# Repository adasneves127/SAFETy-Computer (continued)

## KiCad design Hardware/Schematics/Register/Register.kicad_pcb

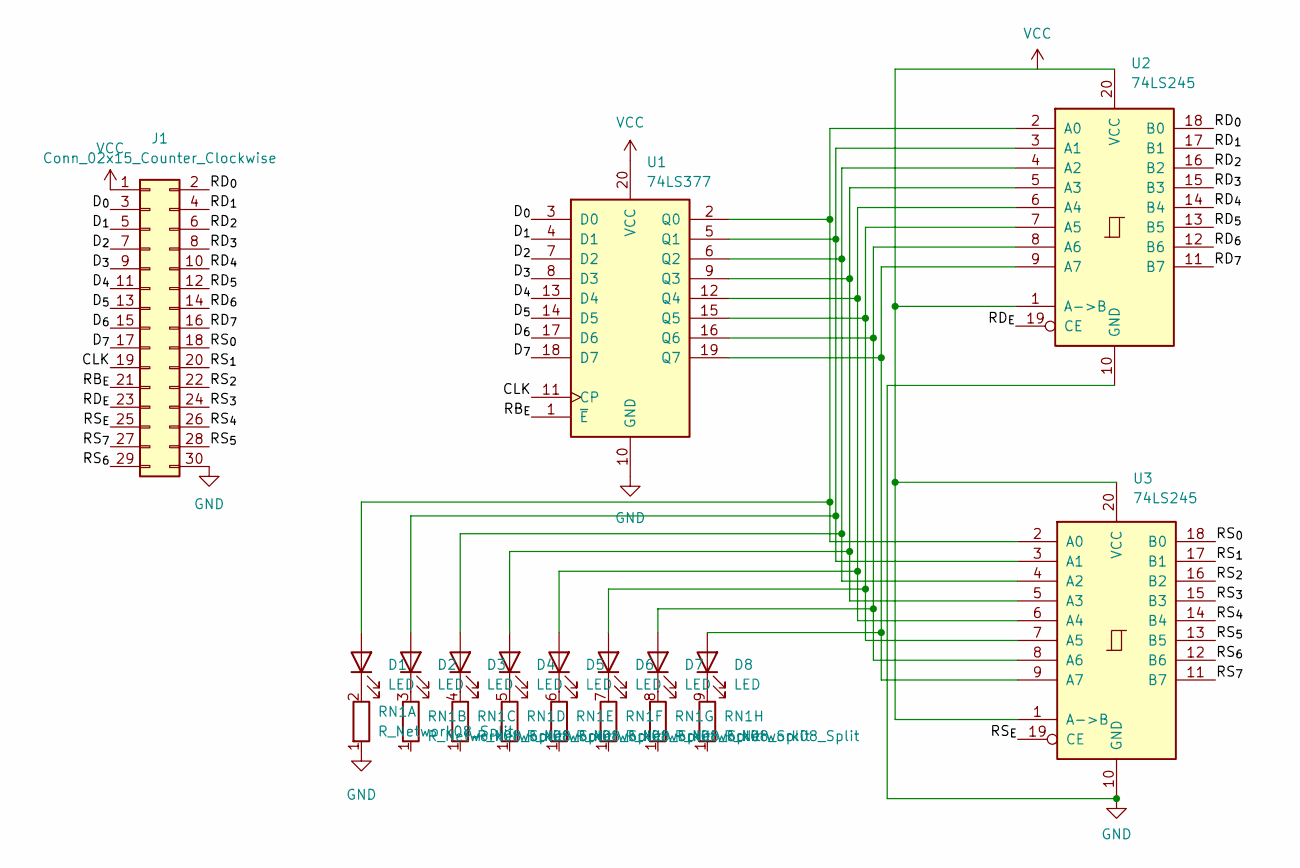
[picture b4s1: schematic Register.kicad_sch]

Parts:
D1, D2, D3, D4, D5, D6, D7, D8: LED; LED_D5.0mm
J1: Conn_02x15_Counter_Clockwise; PinHeader_2x15_P2.54mm_Vertical
RN1: R_Network08_Split; R_Array_SIP9
U1: 74LS377; DIP-20_W7.62mm_Socket_LongPads
U2, U3: 74LS245; DIP-20_W7.62mm_Socket_LongPads

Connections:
/CLK: J1.19, U1.11 (CP)
/D_{0}: J1.3, U1.3 (D0)
/D_{1}: J1.5, U1.4 (D1)
/D_{2}: J1.7, U1.7 (D2)
/D_{3}: J1.9, U1.8 (D3)
/D_{4}: J1.11, U1.13 (D4)
/D_{5}: J1.13, U1.14 (D5)
/D_{6}: J1.15, U1.17 (D6)
/D_{7}: J1.17, U1.18 (D7)
/RB_{E}: J1.21, U1.1 (~E)
/RD_{0}: J1.2, U2.18 (B0)
/RD_{1}: J1.4, U2.17 (B1)
/RD_{2}: J1.6, U2.16 (B2)
/RD_{3}: J1.8, U2.15 (B3)
/RD_{4}: J1.10, U2.14 (B4)
/RD_{5}: J1.12, U2.13 (B5)
/RD_{6}: J1.14, U2.12 (B6)
/RD_{7}: J1.16, U2.11 (B7)
/RD_{E}: J1.23, U2.19 (CE)
/RS_{0}: J1.18, U3.18 (B0)
/RS_{1}: J1.20, U3.17 (B1)
/RS_{2}: J1.22, U3.16 (B2)
/RS_{3}: J1.24, U3.15 (B3)
/RS_{4}: J1.26, U3.14 (B4)
/RS_{5}: J1.28, U3.13 (B5)
/RS_{6}: J1.29, U3.12 (B6)
/RS_{7}: J1.27, U3.11 (B7)
/RS_{E}: J1.25, U3.19 (CE)
GND: J1.30, RN1.1 (R1.1), U1.10 (GND), U2.10 (GND), U3.10 (GND)
unnamed: D1.1 (K), RN1.2 (R1.2)
unnamed: D2.1 (K), RN1.3 (R2.2)
unnamed: D3.1 (K), RN1.4 (R3.2)
unnamed: D4.1 (K), RN1.5 (R4.2)
unnamed: D5.1 (K), RN1.6 (R5.2)
unnamed: D6.1 (K), RN1.7 (R6.2)
unnamed: D7.1 (K), RN1.8 (R7.2)
unnamed: D8.1 (K), RN1.9 (R8.2)
unnamed: D1.2 (A), U1.2 (Q0), U2.2 (A0), U3.2 (A0)
unnamed: D2.2 (A), U1.5 (Q1), U2.3 (A1), U3.3 (A1)
unnamed: D3.2 (A), U1.6 (Q2), U2.4 (A2), U3.4 (A2)
unnamed: D4.2 (A), U1.9 (Q3), U2.5 (A3), U3.5 (A3)
unnamed: D5.2 (A), U1.12 (Q4), U2.6 (A4), U3.6 (A4)
unnamed: D6.2 (A), U1.15 (Q5), U2.7 (A5), U3.7 (A5)
unnamed: D7.2 (A), U1.16 (Q6), U2.8 (A6), U3.8 (A6)
unnamed: D8.2 (A), U1.19 (Q7), U2.9 (A7), U3.9 (A7)

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
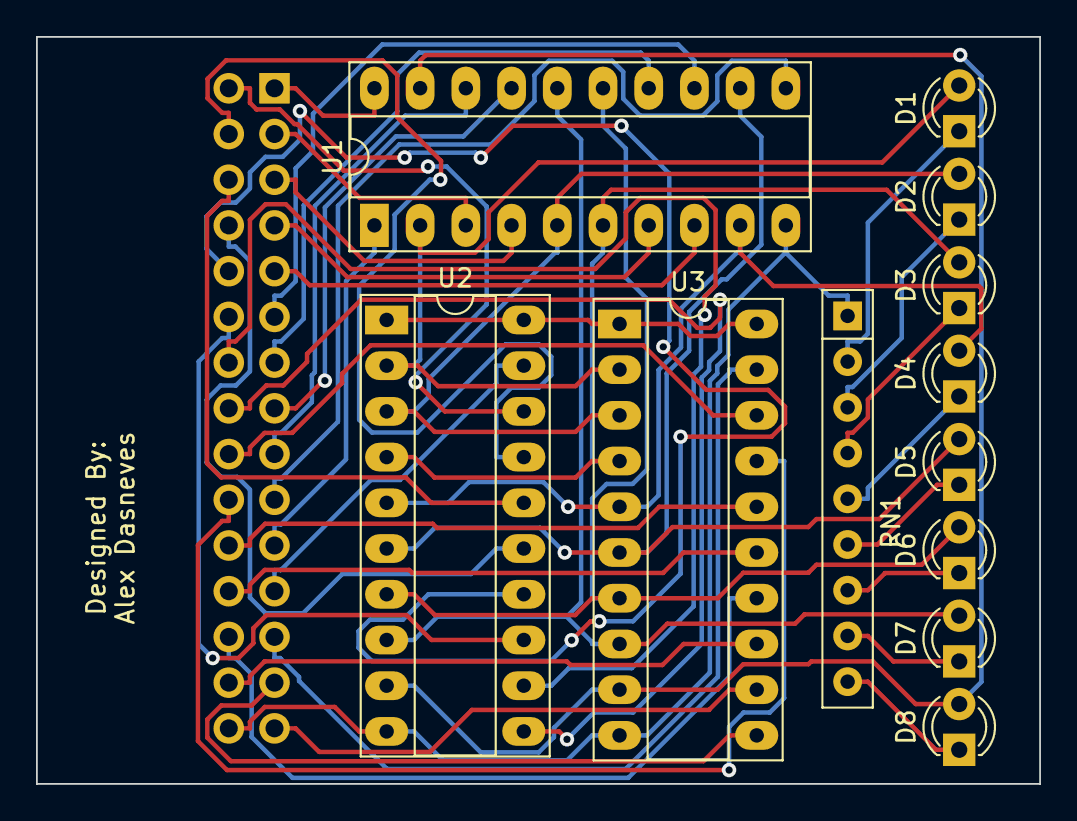
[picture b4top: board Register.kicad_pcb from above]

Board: 2 copper layers, 55.7 x 41.5 mm, 13 parts (1 on the bottom side), 47 nets.

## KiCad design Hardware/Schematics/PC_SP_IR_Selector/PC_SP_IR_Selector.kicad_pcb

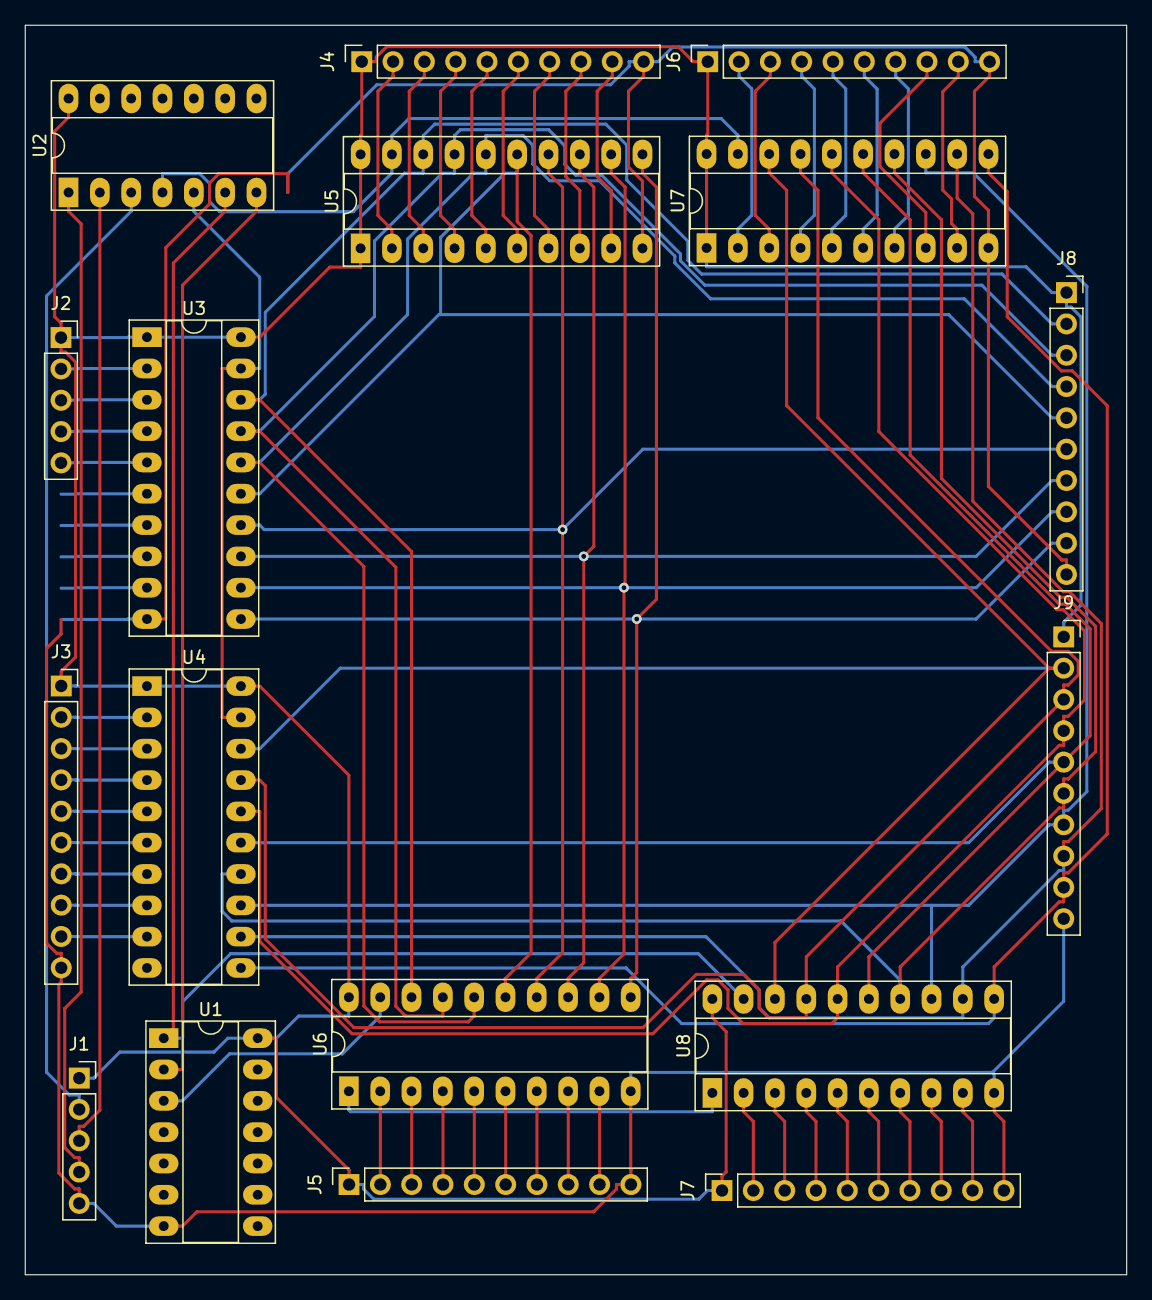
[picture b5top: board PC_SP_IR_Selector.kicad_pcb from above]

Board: 2 copper layers, 89.3 x 101.3 mm, 17 parts (0 on the bottom side), 71 nets.

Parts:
J1: Conn_01x05; PinSocket_1x05_P2.54mm_Vertical
J2: Conn_01x10; PinSocket_1x05_P2.54mm_Vertical
J3, J4, J5, J6, J7, J8, J9: Conn_01x10; PinSocket_1x10_P2.54mm_Vertical
U1: 74LS08; DIP-14_W7.62mm_Socket_LongPads
U2: 74LS139; DIP-14_W7.62mm_Socket_LongPads
U3, U4, U5, U6, U7, U8: 74LS245; DIP-20_W7.62mm_Socket_LongPads

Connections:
GND: J1.5, J3.10, J4.10, J5.10, J6.10, J7.10, J8.10, J9.10, U1.7 (GND), U2.8 (GND), U3.10 (GND), U5.10 (GND), U6.10 (GND), U7.10 (GND), U8.10 (GND)
unnamed: J1.2, U2.3 (A1)
unnamed: J1.3, U2.2 (A0)
unnamed: J1.4, U2.1 (E)
unnamed: J2.2, U3.2 (A0)
unnamed: J2.3, U3.3 (A1)
unnamed: J2.4, U3.4 (A2)
unnamed: J2.5, U3.5 (A3)
unnamed: J3.2, U4.2 (A0)
unnamed: J3.3, U4.3 (A1)
unnamed: J3.4, U4.4 (A2)
unnamed: J3.5, U4.5 (A3)
unnamed: J3.6, U4.6 (A4)
unnamed: J3.7, U4.7 (A5)
unnamed: J3.8, U4.8 (A6)
unnamed: J3.9, U4.9 (A7)
unnamed: J4.2, U5.2 (A0)
unnamed: J4.3, U5.3 (A1)
unnamed: J4.4, U5.4 (A2)
unnamed: J4.5, U5.5 (A3)
unnamed: J4.6, U5.6 (A4)
unnamed: J4.7, U5.7 (A5)
unnamed: J4.8, U5.8 (A6)
unnamed: J4.9, U5.9 (A7)
unnamed: J5.2, U6.2 (A0)
unnamed: J5.3, U6.3 (A1)
unnamed: J5.4, U6.4 (A2)
unnamed: J5.5, U6.5 (A3)
unnamed: J5.6, U6.6 (A4)
unnamed: J5.7, U6.7 (A5)
unnamed: J5.8, U6.8 (A6)
unnamed: J5.9, U6.9 (A7)
unnamed: J6.2, U7.2 (A0)
unnamed: J6.3, U7.3 (A1)
unnamed: J6.4, U7.4 (A2)
unnamed: J6.5, U7.5 (A3)
unnamed: J6.6, U7.6 (A4)
unnamed: J6.7, U7.7 (A5)
unnamed: J6.8, U7.8 (A6)
unnamed: J6.9, U7.9 (A7)
unnamed: J7.2, U8.2 (A0)
unnamed: J7.3, U8.3 (A1)
unnamed: J7.4, U8.4 (A2)
unnamed: J7.5, U8.5 (A3)
unnamed: J7.6, U8.6 (A4)
unnamed: J7.7, U8.7 (A5)
unnamed: J7.8, U8.8 (A6)
unnamed: J7.9, U8.9 (A7)
unnamed: J8.2, U3.18 (B0), U5.18 (B0), U6.18 (B0)
unnamed: J8.3, U3.17 (B1), U5.17 (B1), U6.17 (B1)
unnamed: J8.4, U3.16 (B2), U5.16 (B2), U6.16 (B2)
unnamed: J8.5, U3.15 (B3), U5.15 (B3), U6.15 (B3)
unnamed: J8.6, U3.14 (B4), U5.14 (B4), U6.14 (B4)
unnamed: J8.7, U3.13 (B5), U5.13 (B5), U6.13 (B5)
unnamed: J8.8, U3.12 (B6), U5.12 (B6), U6.12 (B6)
unnamed: J8.9, U3.11 (B7), U5.11 (B7), U6.11 (B7)
unnamed: J9.2, U4.18 (B0), U7.18 (B0), U8.18 (B0)
unnamed: J9.3, U4.17 (B1), U7.17 (B1), U8.17 (B1)
unnamed: J9.4, U4.16 (B2), U7.16 (B2), U8.16 (B2)
unnamed: J9.5, U4.15 (B3), U7.15 (B3), U8.15 (B3)
unnamed: J9.6, U4.14 (B4), U7.14 (B4), U8.14 (B4)
unnamed: J9.7, U4.13 (B5), U7.13 (B5), U8.13 (B5)
unnamed: J9.8, U4.12 (B6), U7.12 (B6), U8.12 (B6)
unnamed: J9.9, U4.11 (B7), U7.11 (B7), U8.11 (B7)
unnamed: U1.1, U2.6 (O2), U8.19 (CE)
unnamed: U1.2, U2.7 (O3)
unnamed: U1.3, U6.19 (CE)
unnamed: U2.4 (O0), U5.19 (CE), U7.19 (CE)
unnamed: U2.5 (O1), U3.19 (CE), U4.19 (CE)
unnamed: U6.1 (A->B), U8.1 (A->B)
VCC: J1.1, J2.1, J3.1, J4.1, J5.1, J6.1, J7.1, J8.1, J9.1, U1.14 (VCC), U3.1 (A->B), U3.20 (VCC), U4.1 (A->B), U4.20 (VCC), U5.1 (A->B), U5.20 (VCC), U6.20 (VCC), U7.1 (A->B), U7.20 (VCC), U8.20 (VCC)

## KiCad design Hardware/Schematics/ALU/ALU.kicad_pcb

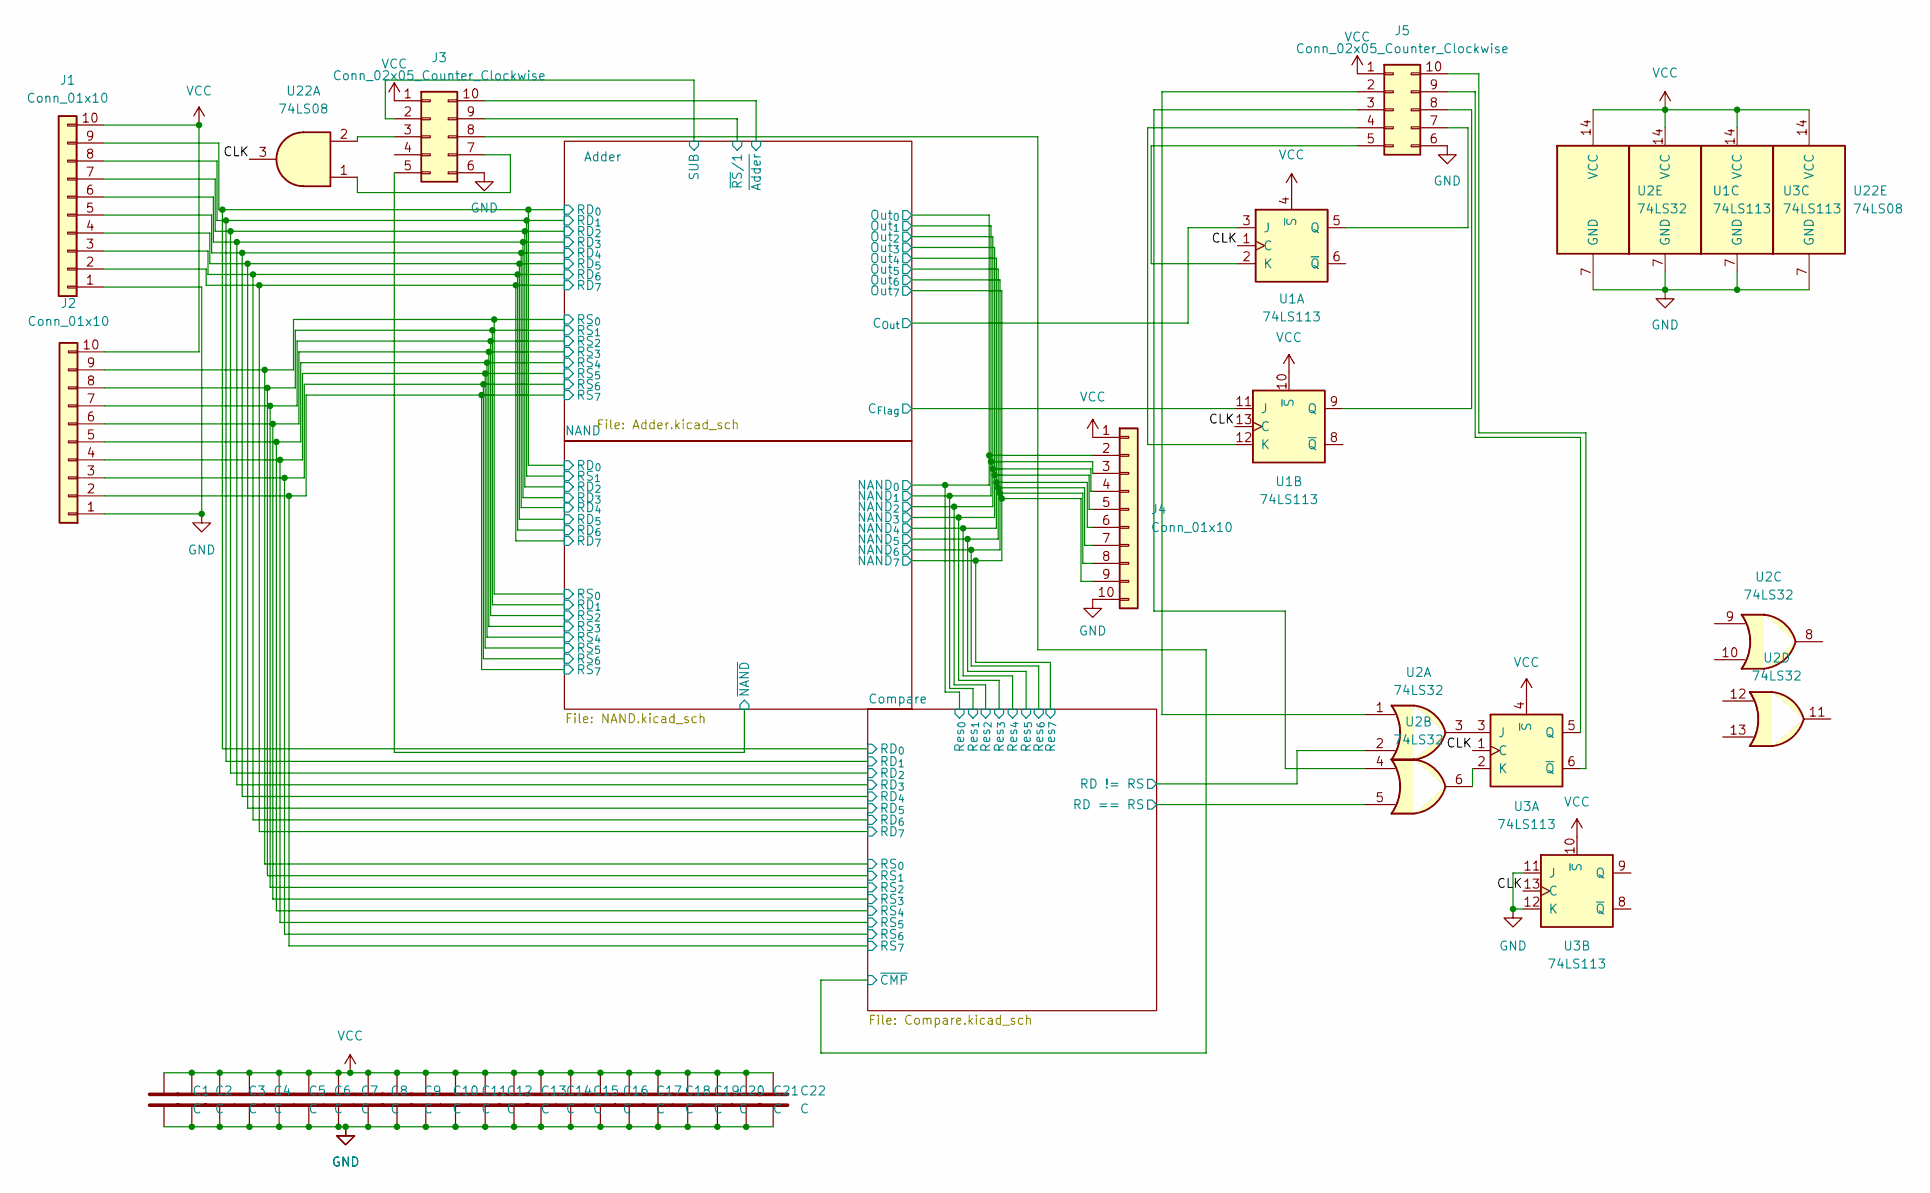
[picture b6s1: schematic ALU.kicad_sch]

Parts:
C1, C2, C3, C4, C5, C6, C7, C8, C9, C10, C11, C12, C13, C14, C15, C16, C17, C18, C19, C20, C21, C22: C; C_Rect_L9.0mm_W2.5mm_P7.50mm_MKT
J1, J2, J4: Conn_01x10; PinHeader_1x10_P2.54mm_Horizontal
J3, J5: Conn_02x05_Counter_Clockwise; PinHeader_2x05_P2.54mm_Horizontal
U1, U3: 74LS113; DIP-14_W7.62mm_Socket_LongPads
U2: 74LS32; DIP-14_W7.62mm_Socket_LongPads
U22: 74LS08; DIP-14_W7.62mm_Socket_LongPads

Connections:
/Adder/C_{Flag}: U1.11 (J); also elsewhere on the board
/Adder/C_{Out}: U1.3 (J); also elsewhere on the board
/Adder/Out_{0}: J4.2; also elsewhere on the board
/Adder/Out_{1}: J4.3; also elsewhere on the board
/Adder/Out_{2}: J4.4; also elsewhere on the board
/Adder/Out_{3}: J4.5; also elsewhere on the board
/Adder/Out_{4}: J4.6; also elsewhere on the board
/Adder/Out_{5}: J4.7; also elsewhere on the board
/Adder/Out_{6}: J4.8; also elsewhere on the board
/Adder/Out_{7}: J4.9; also elsewhere on the board
/Adder/RD_{0}: J1.9; also elsewhere on the board
/Adder/RD_{1}: J1.8; also elsewhere on the board
/Adder/RD_{2}: J1.7; also elsewhere on the board
/Adder/RD_{3}: J1.6; also elsewhere on the board
/Adder/RD_{4}: J1.5; also elsewhere on the board
/Adder/RD_{5}: J1.4; also elsewhere on the board
/Adder/RD_{6}: J1.3; also elsewhere on the board
/Adder/RD_{7}: J1.2; also elsewhere on the board
/Adder/RS_{0}: J2.9; also elsewhere on the board
/Adder/RS_{1}: J2.8; also elsewhere on the board
/Adder/RS_{2}: J2.7; also elsewhere on the board
/Adder/RS_{3}: J2.6; also elsewhere on the board
/Adder/RS_{4}: J2.5; also elsewhere on the board
/Adder/RS_{5}: J2.4; also elsewhere on the board
/Adder/RS_{6}: J2.3; also elsewhere on the board
/Adder/RS_{7}: J2.2; also elsewhere on the board
/Adder/SUB: J3.2; also elsewhere on the board
/Adder/~Adder: J3.10; also elsewhere on the board
/Adder/~RS/1: J3.9; also elsewhere on the board
/CLK: U1.1 (C), U1.13 (C), U3.1 (C), U3.13 (C), U22.3
/Compare/RD != RS: U2.2; also elsewhere on the board
/Compare/RD == RS: U2.5; also elsewhere on the board
/Compare/~CMP: J3.8; also elsewhere on the board
/NAND/~NAND: J3.5; also elsewhere on the board
GND: C1.2, C2.2, C3.2, C4.2, C5.2, C6.2, C7.2, C8.2, C9.2, C10.2, C11.2, C12.2, C13.2, C14.2, C15.2, C16.2, C17.2, C18.2, C19.2, C20.2, C21.2, C22.2, J1.1, J2.1, J3.6, J4.10, J5.6, U1.7 (GND), U2.7 (GND), U3.7 (GND), U3.11 (J), U3.12 (K), U22.7 (GND); also elsewhere on the board
unnamed: J3.3, U22.2
unnamed: J3.7, U22.1
unnamed: J5.2, U2.1
unnamed: J5.3, U2.4
unnamed: J5.4, U1.12 (K)
unnamed: J5.5, U1.2 (K)
unnamed: J5.7, U1.5 (Q)
unnamed: J5.8, U1.9 (Q)
unnamed: J5.9, U3.5 (Q)
unnamed: J5.10, U3.6 (~Q)
unnamed: U2.3, U3.3 (J)
unnamed: U2.6, U3.2 (K)
VCC: C1.1, C2.1, C3.1, C4.1, C5.1, C6.1, C7.1, C8.1, C9.1, C10.1, C11.1, C12.1, C13.1, C14.1, C15.1, C16.1, C17.1, C18.1, C19.1, C20.1, C21.1, C22.1, J1.10, J2.10, J3.1, J4.1, J5.1, U1.4 (~S), U1.10 (~S), U1.14 (VCC), U2.14 (VCC), U3.4 (~S), U3.10 (~S), U3.14 (VCC), U22.14 (VCC); also elsewhere on the board

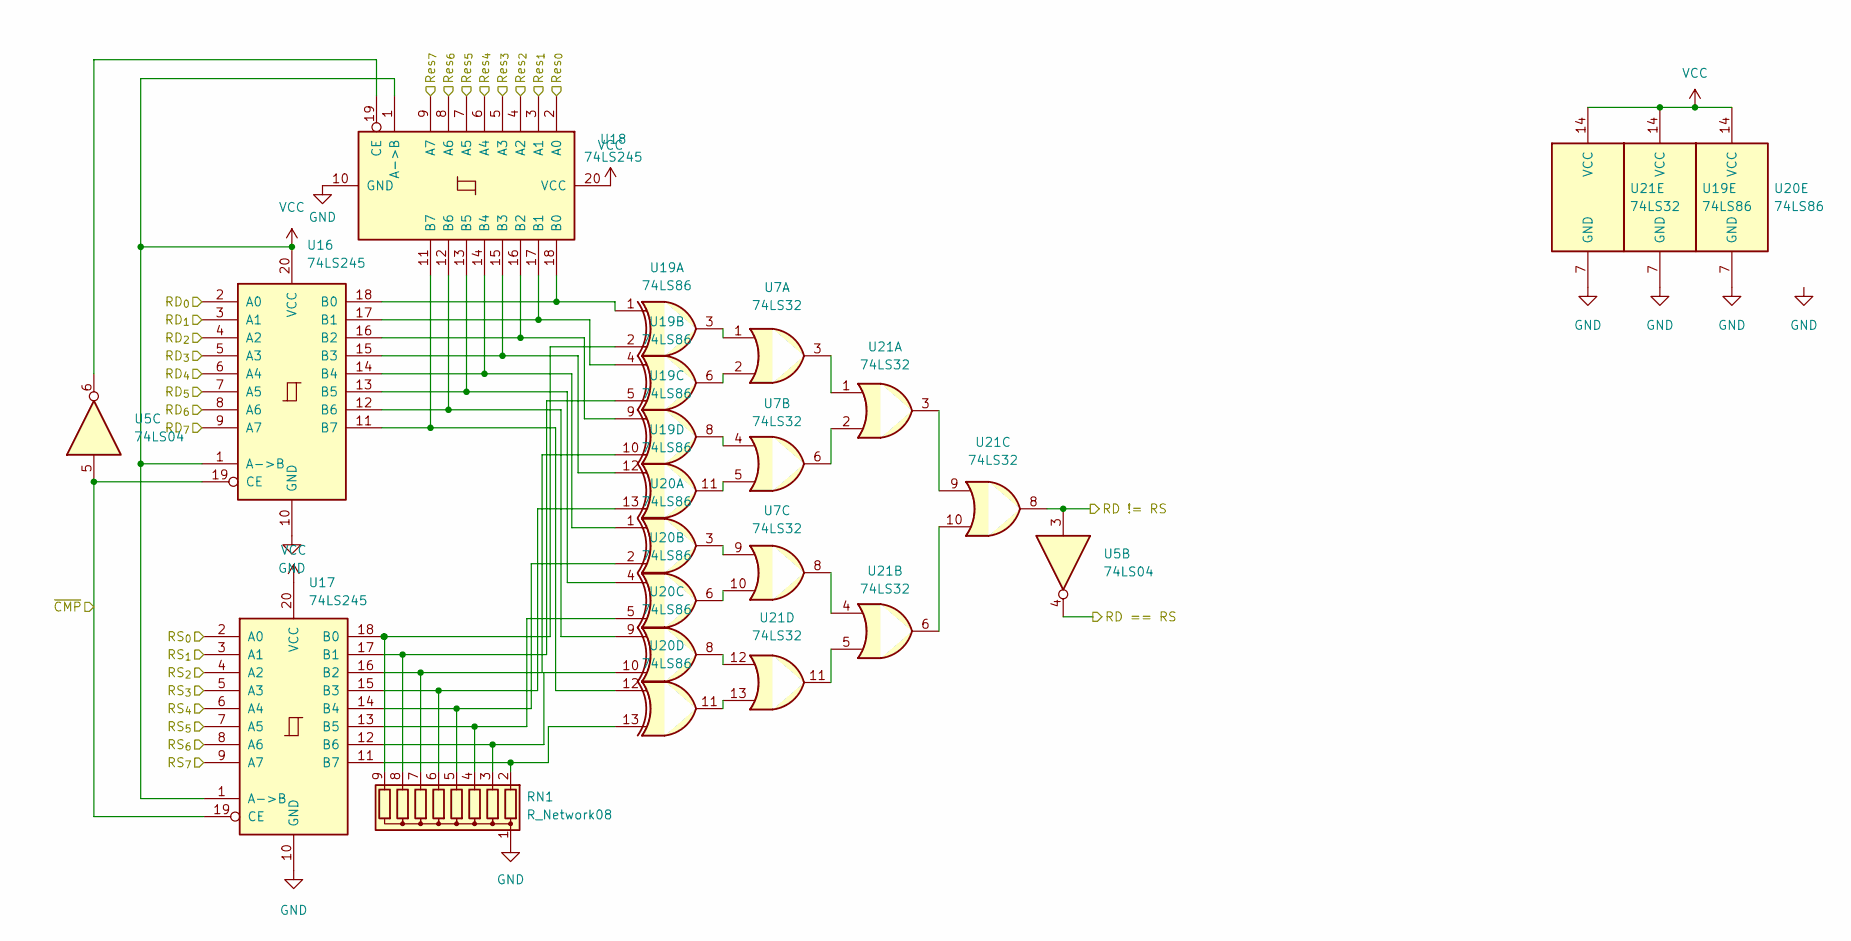
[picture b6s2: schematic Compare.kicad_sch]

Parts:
RN1: R_Network08; R_Array_SIP9
U5: 74LS04; DIP-14_W7.62mm_Socket_LongPads
U7, U21: 74LS32; DIP-14_W7.62mm_Socket_LongPads
U16, U17, U18: 74LS245; DIP-20_W7.62mm_Socket_LongPads
U19, U20: 74LS86; DIP-14_W7.62mm_Socket_LongPads

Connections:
/Adder/Out_{0}: U18.2 (A0); also elsewhere on the board
/Adder/Out_{1}: U18.3 (A1); also elsewhere on the board
/Adder/Out_{2}: U18.4 (A2); also elsewhere on the board
/Adder/Out_{3}: U18.5 (A3); also elsewhere on the board
/Adder/Out_{4}: U18.6 (A4); also elsewhere on the board
/Adder/Out_{5}: U18.7 (A5); also elsewhere on the board
/Adder/Out_{6}: U18.8 (A6); also elsewhere on the board
/Adder/Out_{7}: U18.9 (A7); also elsewhere on the board
/Adder/RD_{0}: U16.2 (A0); also elsewhere on the board
/Adder/RD_{1}: U16.3 (A1); also elsewhere on the board
/Adder/RD_{2}: U16.4 (A2); also elsewhere on the board
/Adder/RD_{3}: U16.5 (A3); also elsewhere on the board
/Adder/RD_{4}: U16.6 (A4); also elsewhere on the board
/Adder/RD_{5}: U16.7 (A5); also elsewhere on the board
/Adder/RD_{6}: U16.8 (A6); also elsewhere on the board
/Adder/RD_{7}: U16.9 (A7); also elsewhere on the board
/Adder/RS_{0}: U17.2 (A0); also elsewhere on the board
/Adder/RS_{1}: U17.3 (A1); also elsewhere on the board
/Adder/RS_{2}: U17.4 (A2); also elsewhere on the board
/Adder/RS_{3}: U17.5 (A3); also elsewhere on the board
/Adder/RS_{4}: U17.6 (A4); also elsewhere on the board
/Adder/RS_{5}: U17.7 (A5); also elsewhere on the board
/Adder/RS_{6}: U17.8 (A6); also elsewhere on the board
/Adder/RS_{7}: U17.9 (A7); also elsewhere on the board
/Compare/RD != RS: U5.3, U21.8; also elsewhere on the board
/Compare/RD == RS: U5.4; also elsewhere on the board
/Compare/~CMP: U5.5, U16.19 (CE), U17.19 (CE); also elsewhere on the board
GND: RN1.1 (common), U16.10 (GND), U17.10 (GND), U18.10 (GND), U19.7 (GND), U20.7 (GND), U21.7 (GND); also elsewhere on the board
unnamed: RN1.2 (R1), U17.11 (B7), U20.13
unnamed: RN1.3 (R2), U17.12 (B6), U20.10
unnamed: RN1.4 (R3), U17.13 (B5), U20.5
unnamed: RN1.5 (R4), U17.14 (B4), U20.2
unnamed: RN1.6 (R5), U17.15 (B3), U19.13
unnamed: RN1.7 (R6), U17.16 (B2), U19.10
unnamed: RN1.8 (R7), U17.17 (B1), U19.5
unnamed: RN1.9 (R8), U17.18 (B0), U19.2
unnamed: U16.11 (B7), U18.11 (B7), U20.12
unnamed: U16.12 (B6), U18.12 (B6), U20.9
unnamed: U16.13 (B5), U18.13 (B5), U20.4
unnamed: U16.14 (B4), U18.14 (B4), U20.1
unnamed: U16.15 (B3), U18.15 (B3), U19.12
unnamed: U16.16 (B2), U18.16 (B2), U19.9
unnamed: U16.17 (B1), U18.17 (B1), U19.4
unnamed: U16.18 (B0), U18.18 (B0), U19.1
unnamed: U5.6, U18.19 (CE)
unnamed: U7.1, U19.3
unnamed: U7.2, U19.6
unnamed: U7.4, U19.8
unnamed: U7.5, U19.11
unnamed: U7.9, U20.3
unnamed: U7.10, U20.6
unnamed: U20.8, U21.12
unnamed: U20.11, U21.13
unnamed: U7.3, U21.1
unnamed: U7.6, U21.2
unnamed: U21.3, U21.9
unnamed: U7.8, U21.4
unnamed: U21.6, U21.10
unnamed: U21.5, U21.11
VCC: U16.1 (A->B), U16.20 (VCC), U17.1 (A->B), U17.20 (VCC), U18.1 (A->B), U18.20 (VCC), U19.14 (VCC), U20.14 (VCC), U21.14 (VCC); also elsewhere on the board

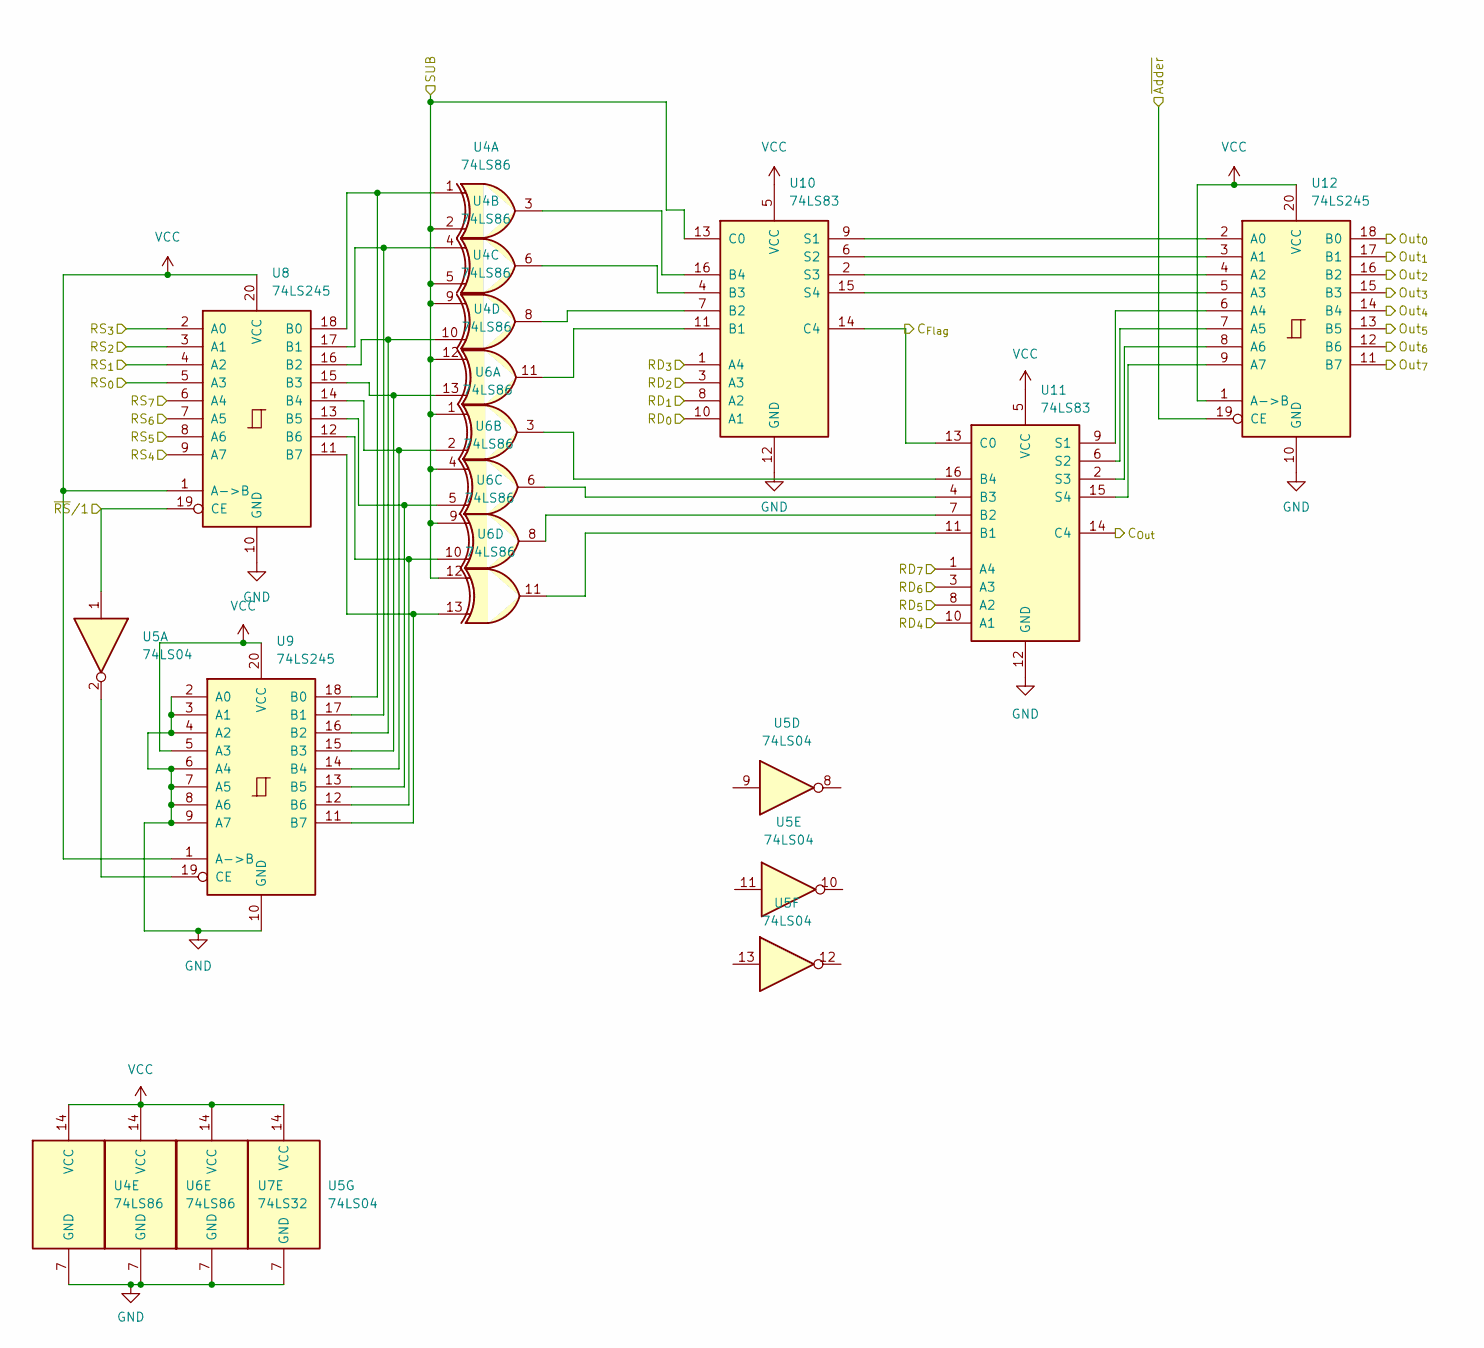
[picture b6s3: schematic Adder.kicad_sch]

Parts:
U4, U6: 74LS86; DIP-14_W7.62mm_Socket_LongPads
U5: 74LS04; DIP-14_W7.62mm_Socket_LongPads
U7: 74LS32; DIP-14_W7.62mm_Socket_LongPads
U8, U9, U12: 74LS245; DIP-20_W7.62mm_Socket_LongPads
U10, U11: 74LS83; DIP-16_W7.62mm_Socket_LongPads

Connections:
/Adder/C_{Flag}: U10.14 (C4), U11.13 (C0); also elsewhere on the board
/Adder/C_{Out}: U11.14 (C4); also elsewhere on the board
/Adder/Out_{0}: U12.18 (B0); also elsewhere on the board
/Adder/Out_{1}: U12.17 (B1); also elsewhere on the board
/Adder/Out_{2}: U12.16 (B2); also elsewhere on the board
/Adder/Out_{3}: U12.15 (B3); also elsewhere on the board
/Adder/Out_{4}: U12.14 (B4); also elsewhere on the board
/Adder/Out_{5}: U12.13 (B5); also elsewhere on the board
/Adder/Out_{6}: U12.12 (B6); also elsewhere on the board
/Adder/Out_{7}: U12.11 (B7); also elsewhere on the board
/Adder/RD_{0}: U10.10 (A1); also elsewhere on the board
/Adder/RD_{1}: U10.8 (A2); also elsewhere on the board
/Adder/RD_{2}: U10.3 (A3); also elsewhere on the board
/Adder/RD_{3}: U10.1 (A4); also elsewhere on the board
/Adder/RD_{4}: U11.10 (A1); also elsewhere on the board
/Adder/RD_{5}: U11.8 (A2); also elsewhere on the board
/Adder/RD_{6}: U11.3 (A3); also elsewhere on the board
/Adder/RD_{7}: U11.1 (A4); also elsewhere on the board
/Adder/RS_{0}: U8.5 (A3); also elsewhere on the board
/Adder/RS_{1}: U8.4 (A2); also elsewhere on the board
/Adder/RS_{2}: U8.3 (A1); also elsewhere on the board
/Adder/RS_{3}: U8.2 (A0); also elsewhere on the board
/Adder/RS_{4}: U8.9 (A7); also elsewhere on the board
/Adder/RS_{5}: U8.8 (A6); also elsewhere on the board
/Adder/RS_{6}: U8.7 (A5); also elsewhere on the board
/Adder/RS_{7}: U8.6 (A4); also elsewhere on the board
/Adder/SUB: U4.2, U4.5, U4.9, U4.12, U6.1, U6.4, U6.9, U6.12, U10.13 (C0); also elsewhere on the board
/Adder/~Adder: U12.19 (CE); also elsewhere on the board
/Adder/~RS/1: U5.1, U8.19 (CE); also elsewhere on the board
GND: U4.7 (GND), U5.7 (GND), U6.7 (GND), U7.7 (GND), U8.10 (GND), U9.2 (A0), U9.3 (A1), U9.4 (A2), U9.6 (A4), U9.7 (A5), U9.8 (A6), U9.9 (A7), U9.10 (GND), U10.12 (GND), U11.12 (GND), U12.10 (GND); also elsewhere on the board
unnamed: U4.1, U8.18 (B0), U9.18 (B0)
unnamed: U4.4, U8.17 (B1), U9.17 (B1)
unnamed: U4.10, U8.16 (B2), U9.16 (B2)
unnamed: U4.13, U8.15 (B3), U9.15 (B3)
unnamed: U5.2, U9.19 (CE)
unnamed: U6.2, U8.14 (B4), U9.14 (B4)
unnamed: U6.5, U8.13 (B5), U9.13 (B5)
unnamed: U6.10, U8.12 (B6), U9.12 (B6)
unnamed: U6.13, U8.11 (B7), U9.11 (B7)
unnamed: U10.2 (S3), U12.4 (A2)
unnamed: U4.6, U10.4 (B3)
unnamed: U10.6 (S2), U12.3 (A1)
unnamed: U4.8, U10.7 (B2)
unnamed: U10.9 (S1), U12.2 (A0)
unnamed: U4.11, U10.11 (B1)
unnamed: U10.15 (S4), U12.5 (A3)
unnamed: U4.3, U10.16 (B4)
unnamed: U11.2 (S3), U12.8 (A6)
unnamed: U6.6, U11.4 (B3)
unnamed: U11.6 (S2), U12.7 (A5)
unnamed: U6.8, U11.7 (B2)
unnamed: U11.9 (S1), U12.6 (A4)
unnamed: U6.11, U11.11 (B1)
unnamed: U11.15 (S4), U12.9 (A7)
unnamed: U6.3, U11.16 (B4)
VCC: U4.14 (VCC), U5.14 (VCC), U6.14 (VCC), U7.14 (VCC), U8.1 (A->B), U8.20 (VCC), U9.1 (A->B), U9.5 (A3), U9.20 (VCC), U10.5 (VCC), U11.5 (VCC), U12.1 (A->B), U12.20 (VCC); also elsewhere on the board

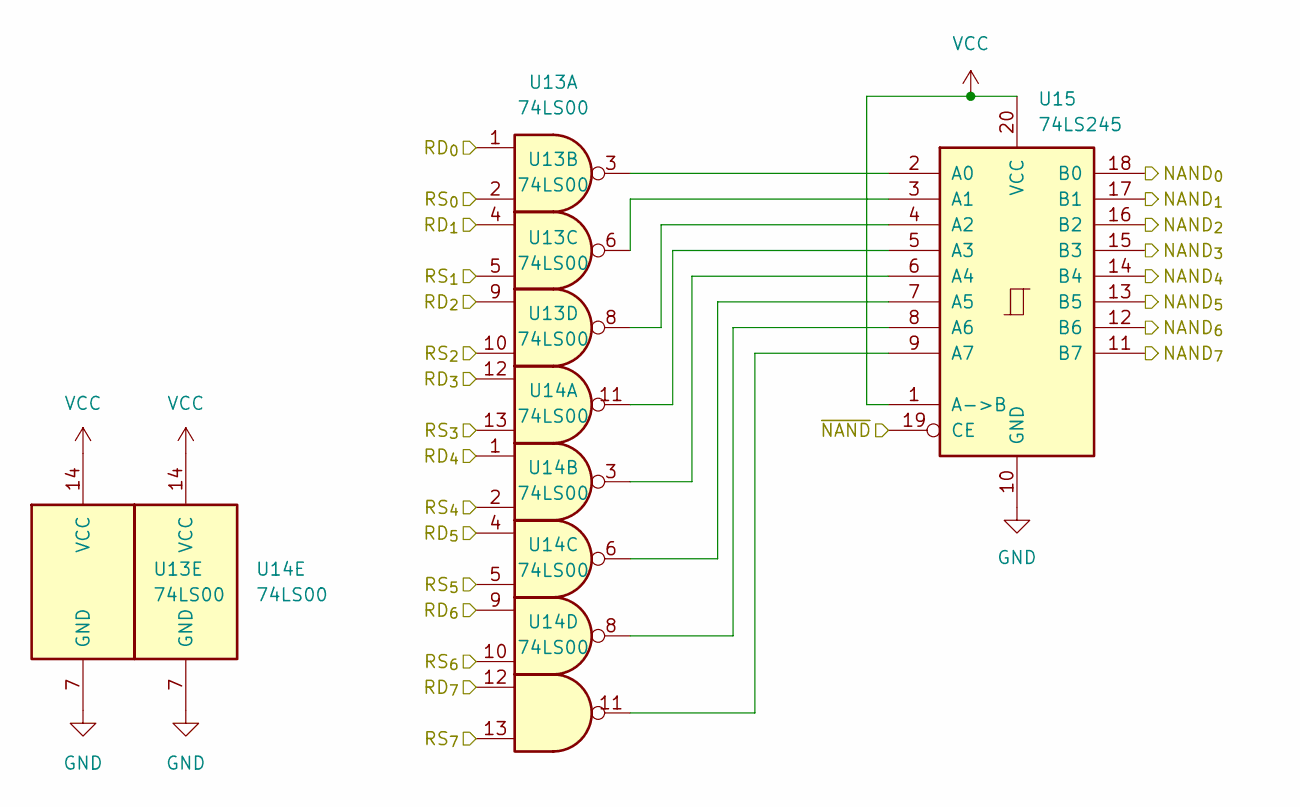
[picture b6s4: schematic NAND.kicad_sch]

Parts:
U13, U14: 74LS00; DIP-14_W7.62mm_Socket_LongPads
U15: 74LS245; DIP-20_W7.62mm_Socket_LongPads

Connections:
/Adder/Out_{0}: U15.18 (B0); also elsewhere on the board
/Adder/Out_{1}: U15.17 (B1); also elsewhere on the board
/Adder/Out_{2}: U15.16 (B2); also elsewhere on the board
/Adder/Out_{3}: U15.15 (B3); also elsewhere on the board
/Adder/Out_{4}: U15.14 (B4); also elsewhere on the board
/Adder/Out_{5}: U15.13 (B5); also elsewhere on the board
/Adder/Out_{6}: U15.12 (B6); also elsewhere on the board
/Adder/Out_{7}: U15.11 (B7); also elsewhere on the board
/Adder/RD_{0}: U13.1; also elsewhere on the board
/Adder/RD_{1}: U13.5; also elsewhere on the board
/Adder/RD_{2}: U13.9; also elsewhere on the board
/Adder/RD_{3}: U13.12; also elsewhere on the board
/Adder/RD_{4}: U14.1; also elsewhere on the board
/Adder/RD_{5}: U14.4; also elsewhere on the board
/Adder/RD_{6}: U14.9; also elsewhere on the board
/Adder/RD_{7}: U14.12; also elsewhere on the board
/Adder/RS_{0}: U13.2; also elsewhere on the board
/Adder/RS_{1}: U13.4; also elsewhere on the board
/Adder/RS_{2}: U13.10; also elsewhere on the board
/Adder/RS_{3}: U13.13; also elsewhere on the board
/Adder/RS_{4}: U14.2; also elsewhere on the board
/Adder/RS_{5}: U14.5; also elsewhere on the board
/Adder/RS_{6}: U14.10; also elsewhere on the board
/Adder/RS_{7}: U14.13; also elsewhere on the board
/NAND/~NAND: U15.19 (CE); also elsewhere on the board
GND: U13.7 (GND), U14.7 (GND), U15.10 (GND); also elsewhere on the board
unnamed: U13.3, U15.2 (A0)
unnamed: U13.6, U15.3 (A1)
unnamed: U13.8, U15.4 (A2)
unnamed: U13.11, U15.5 (A3)
unnamed: U14.3, U15.6 (A4)
unnamed: U14.6, U15.7 (A5)
unnamed: U14.8, U15.8 (A6)
unnamed: U14.11, U15.9 (A7)
VCC: U13.14 (VCC), U14.14 (VCC), U15.1 (A->B), U15.20 (VCC); also elsewhere on the board

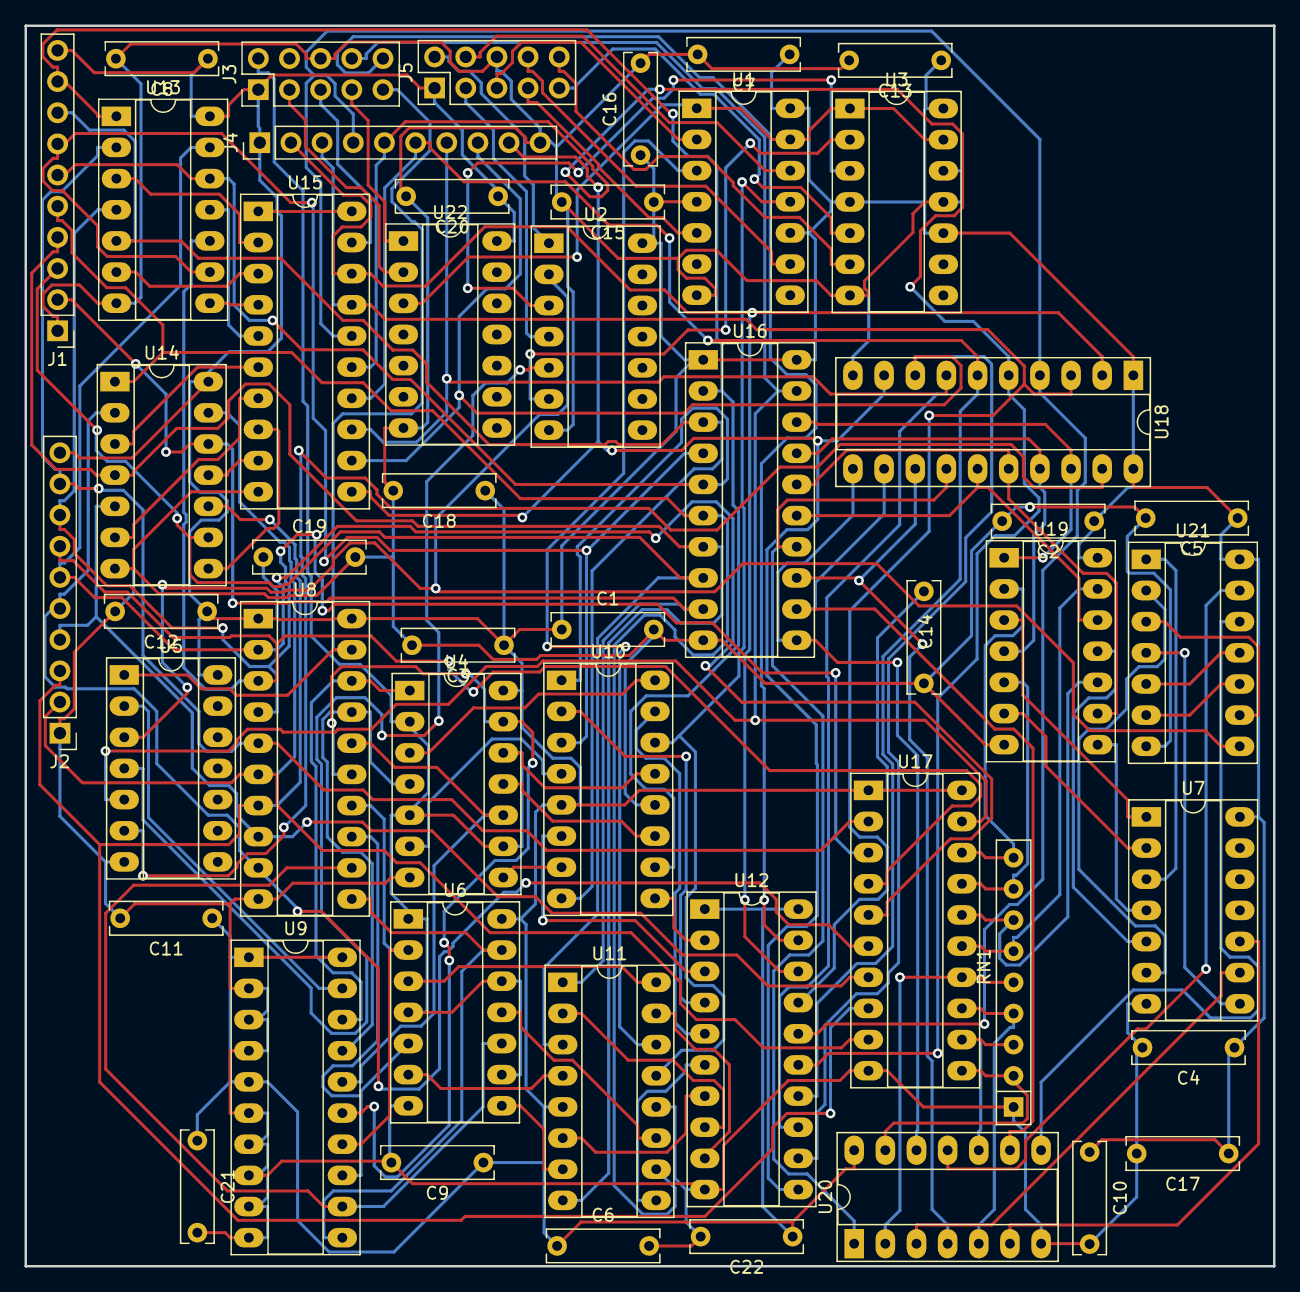
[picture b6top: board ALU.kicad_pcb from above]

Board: 2 copper layers, 101.8 x 101.1 mm, 50 parts (0 on the bottom side), 112 nets.
